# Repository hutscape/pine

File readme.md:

# Pine

> 🌲 Indoor Infrared receiver and transmitter with temperature sensor 🎐

Visit [hutscape.com/pine](https://hutscape.com/pine) for more details.

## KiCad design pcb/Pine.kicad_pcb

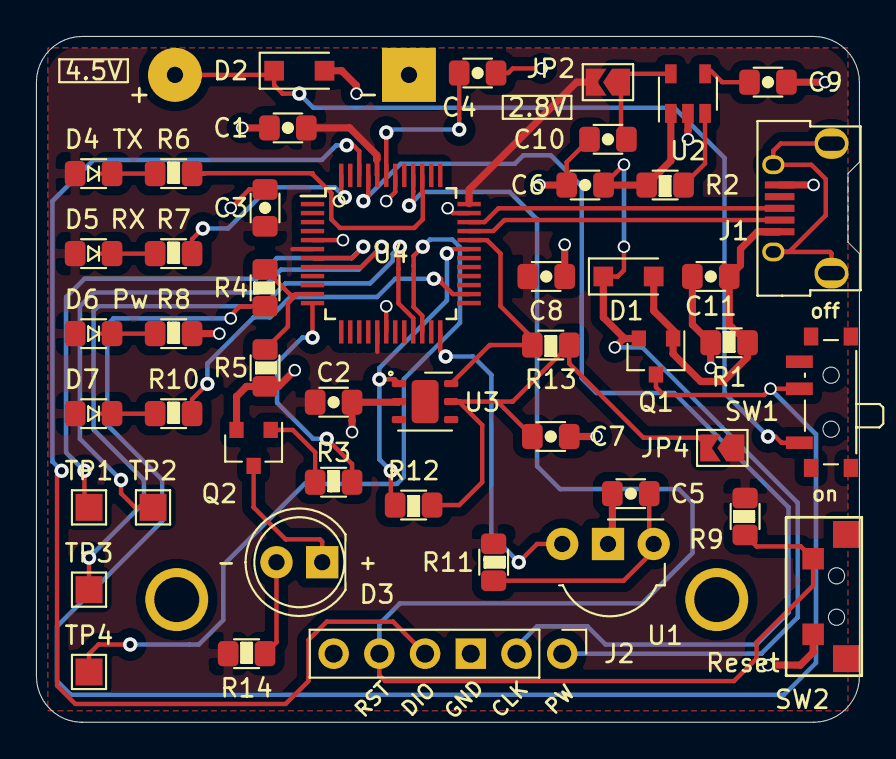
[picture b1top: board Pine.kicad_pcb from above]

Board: 2 copper layers, 45.7 x 38.1 mm, 49 parts (0 on the bottom side), 36 nets.

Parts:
C1, C2, C3: 100nF; C_0805_2012Metric_Pad1.15x1.40mm_HandSolder
C4, C5, C6, C7, C10: 1uF; C_0805_2012Metric_Pad1.15x1.40mm_HandSolder
C8, C11: 10uF; C_0805_2012Metric_Pad1.15x1.40mm_HandSolder
C9: 10nF; C_0805_2012Metric_Pad1.15x1.40mm_HandSolder
D1, D2: Schottky diode; D_SOD-123F
D3: IR LED Emitter; LED_D5.0mm_IRGrey
D4, D5, D6, D7: LED Yellow; LED_0805_2012Metric_Pad1.15x1.40mm_HandSolder
J1: USB Micro type-B; USB_Micro-B_Horizontal-U254-051T-4BH23-S2B
J2: 01x06 Male conn; PinHeader_1x06_P2.54mm_Vertical
J3: Battery connector; BatteryHolder_Takachi_SN3-3PC_3AA
JP2, JP4: Open solder jumper; SolderJumper-2_P1.3mm_Open_TrianglePad1.0x1.5mm
Q1: p-channel MOSFET; SOT-23
Q2: NPN Transistor; SOT-23
R1, R9, R12, R13: 10k; R_0805_2012Metric_Pad1.15x1.40mm_HandSolder
R2, R4, R5: 100k; R_0805_2012Metric_Pad1.15x1.40mm_HandSolder
R3, R6, R7, R8, R10, R11: 470R; R_0805_2012Metric_Pad1.15x1.40mm_HandSolder
R14: 0R; R_0805_2012Metric_Pad1.15x1.40mm_HandSolder
SW1: Switch; SW_SPDT_PCM12
SW2: Push button; Tactile_pushbutton
TP1, TP2, TP3, TP4: TestPoint_Probe; TestPoint_Pad_1.5x1.5mm
U1: IR Receiver; Vishay_MOLD-3Pin
U2: LDO; SOT-23-5
U3: Temperature sensor; DFN-6-1EP_3x3mm_P1mm_EP1.5x2.4mm
U4: MCU; TQFP-48_7x7mm_P0.5mm

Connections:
+2V8: C1.1, C2.1, C3.1, C8.1, D4.2, D5.2, D6.2, D7.2, JP2.2, JP4.1, R9.2, R11.1, R14.1, U4.6, U4.17, U4.36, U4.44
/Batt: R4.2, R5.1, U4.11
/IR_Emitter: R3.2, U4.12
/IR_Receiver: U1.1, U4.24
/LED: R10.2, U4.26
/RST: J2.5, R9.1, SW2.1, U4.40
/RX_LED: R7.2, U4.48
/SCL: R13.2, U3.6, U4.32
/SDA: R12.2, U3.1, U4.31
/SWCLK: J2.2, U4.45
/SWDIO: J2.4, U4.46
/SWD_POWER_IN: C6.1, D1.1, J2.1, Q1.2, R2.2, U2.1
/TX_LED: R6.2, U4.39
/USB_D+: J1.3, U4.34
/USB_D-: J1.2, U4.33
/VBAT: Q1.3, R4.1, SW1.2
GND: C1.2, C2.2, C3.2, C4.1, C5.2, C6.2, C7.2, C8.2, C9.2, C10.2, C11.2, D2.2, J1.5, J2.3, J3.2, Q2.2, R1.1, R5.2, R8.2, SW2.2, U1.2, U2.2, U3.2, U4.5, U4.18, U4.35, U4.42
unnamed: C4.2, U4.43
unnamed: C5.1, R11.2, U1.3
unnamed: C7.1, JP4.2, R12.1, R13.1, U3.5
unnamed: C9.1, U2.4
unnamed: C10.1, JP2.1, U2.5
unnamed: C11.1, D1.2, J1.1, Q1.1, R1.2
unnamed: D2.1, J3.1, SW1.1
unnamed: D3.1, Q2.3
unnamed: D3.2, R14.2
unnamed: D4.1, R6.1
unnamed: D5.1, R7.1
unnamed: D6.1, R8.1
unnamed: D7.1, R10.1
unnamed: Q2.1, R3.1
unnamed: R2.1, U2.3
unnamed: TP1.1, U4.7
unnamed: TP2.1, U4.8
unnamed: TP3.1, U4.21
unnamed: TP4.1, U4.22

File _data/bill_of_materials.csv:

"Designator","Value","Qty","Package","Category","Stock","Manufacturer","MPN","Datasheet","Vendor","Link","Unit","Total","MOQ","Description","DNP"
"C3, C2, C1, ","100nF","3","0805","Electronics","53","Murata Electronics","GCM21BR72A104KA37L","https://www.mouser.sg/datasheet/2/281/murata_03122018_GCM_Se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","LCSC","https://lcsc.com/product-detail/Multilayer-Ceramic-Capacitor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","0.030","0.09","20","C_Small: Unpolarized capacitor, small symbol",""
"C4, C5, C7, C6, C10, ","1uF","5","0805","Electronics","17","","","","Internal stock","","0","0.0","","C_Small: Unpolarized capacitor, small symbol",""
"C8, C11, ","10uF","2","0805","Electronics","30","","","","Internal stock","","0","0.0","","C_Small: Unpolarized capacitor, small symbol",""
"C9, ","10nF","1","0805","Electronics","55","Walsin Tech Corp","0805B103K631CT","https://datasheet.lcsc.com/szlcsc/1811301232_Huaxin-S-T-0805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","LCSC","https://lcsc.com/product-detail/Multilayer-Ceramic-Capacitor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","0.026","0.03","20","C_Small: Unpolarized capacitor, small symbol",""
"D1, D2, ","Schottky diode","2","SOD-123F ","Electronics","52","Nexperia","PMEG3020EH","https://datasheet.lcsc.com/szlcsc/ON-Semicon-ON-MBR230LSFT1G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","RS Components","https://sg.rs-online.com/web/p/rectifier-diodes-schottky-dio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","0.388","0.78","20","D_Schottky: Schottky diode",""
"D3, ","IR LED Emitter","1","TH","Electronics","39","ROHM","SIR-56ST3F ","https://docs-apac.rs-online.com/webdocs/1674/0900766b816747ad.pdf","RS Components","https://sg.rs-online.com/web/p/ir-leds/1780575/?sra=pstk","0.778","0.78","10","LD274: 950nm IR-LED, 5mm",""
"D4, D5, D6, D7, ","LED Yellow","4","0805","Electronics","54","Everlight Elec","17-215UYC/S530-A3/TR8","https://datasheet.lcsc.com/szlcsc/Everlight-Elec-17-215UYC-S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","LCSC","https://lcsc.com/product-detail/Light-Emitting-Diodes-LED_08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","0.058","0.23","10","LED: Light emitting diode","D4, D5, "
"J1, ","USB Micro type-B","1","SMD","Connector","60","Jing Extension of the Electronic Co.","C10418","https://datasheet.lcsc.com/szlcsc/Jing-Extension-of-the-Elec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","LCSC","https://lcsc.com/product-detail/USB-Connectors_Jing-Extensio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","0.079","0.08","5","USB_B_Micro: USB Micro Type B connector",""
"J2, ","01x06 Male conn","1","TH","Connector","","","","","DNP","","","0","","Conn_01x06_Male: Generic connector, single row, 01x06, script generated (kicad-library-utils/schlib/autogen/connector/)","J2, "
"J3, ","Battery connector","1","TH","Connector","","Takachi Electric Industrial","SN3-3PC","https://docs-apac.rs-online.com/webdocs/1659/0900766b81659aed.pdf","RS Components","https://sg.rs-online.com/web/p/products/1756075","2.484","2.48","1","Conn_01x02_Male: Generic connector, single row, 01x02, script generated (kicad-library-utils/schlib/autogen/connector/)",""
"JP2, JP4, ","Open solder jumper","2","Solder","Electronics","","","","","DNP","","","0","","SolderJumper_2_Open: Solder Jumper, 2-pole, open","JP2, JP4, "
"Q1, ","p-channel MOSFET","1","SOT-23","Electronics","49","Nexperia","BSH203,215 ","https://docs-apac.rs-online.com/webdocs/0f74/0900766b80f74f2c.pdf","RS Components","https://sg.rs-online.com/web/p/mosfets/7258366/","0.312","0.31","20","BSS83P: -0.33A Id, -60V Vds, P-Channel MOSFET, SOT-23-3",""
"Q2, ","NPN Transistor","1","SOT-23","Electronics","58","ON Semiconductor","BC817-25LT3G","https://datasheet.lcsc.com/szlcsc/ON-Semicon-ON-BC817-25LT3G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","LCSC","https://lcsc.com/product-detail/Transistors-NPN-PNP_ON-Semic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","0.021","0.02","5","2N2219: 800mA Ic, 50V Vce, NPN Transistor, TO-39",""
"R2, R4, R5, ","100k","3","0805","Electronics","56","RALEC","RTT051003BTP","https://datasheet.lcsc.com/szlcsc/RALEC-RTT051003BTP_C312260.pdf","LCSC","https://lcsc.com/product-detail/Others_RALEC-RTT051003BTP_C3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","0.042","0.13","20","R_Small: Resistor, small symbol",""
"R9, R1, R12, R13, ","10k","4","0805","Electronics","31","","","","Internal stock","","","0","","R_Small: Resistor, small symbol",""
"R10, R11, R3, R8, R7, R6, ","470R","6","0805","Electronics","57","Walsin Tech Corp","WR08X4700FTL","https://datasheet.lcsc.com/szlcsc/Huaxin-S-T-WR08X4700FTL_C1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","LCSC","https://lcsc.com/product-detail/Chip-Resistor-Surface-Mount_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","0.0050 ","0.03","50","R_Small: Resistor, small symbol","R11, R7, R6, "
"R14, ","0R","1","","Electronics","15","","","","Internal stock","","","0","","R_Small: Resistor, small symbol","R14, "
"SW1, ","Switch","1","SMD","Connector","40","","","","Internal stock","","","0","","SW_SPST: Single Pole Single Throw (SPST) switch",""
"SW2, ","Push button","1","SMD","Connector","14","","","","Internal stock","","","0","","SW_Push: Push button switch, generic, two pins",""
"TP1, TP2, TP3, TP4, ","TestPoint_Probe","4","","Electronics","","","","","","","","0","","TestPoint_Probe: test point (alternative probe-style design)","TP1, TP2, TP3, TP4, "
"U1, ","IR Receiver","1","TH","Electronics","38","Vishay","TSOP4838","https://docs-apac.rs-online.com/webdocs/0e30/0900766b80e30b9e.pdf","RS Components","https://sg.rs-online.com/web/p/ir-receivers/7085115/?sra=pstk","1.876","1.88","5","TSOP43xx: IR Receiver Modules for Remote Control Systems",""
"U2, ","LDO","1","SOT-23","Electronics","50","STMicroelectronics","LD3985M28R_SOT23","https://docs-apac.rs-online.com/webdocs/151f/0900766b8151fea1.pdf","RS Components","https://sg.rs-online.com/web/p/low-dropout-voltage-regulator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","0.32","0.32","","LD3985M28R_SOT23: 150mA Low Dropout Voltage Regulator, Fixed Output 2.8V, SOT-23-5",""
"U3, ","Temperature sensor","1","DFN","Electronics","5","Si Labs","Si7021-A20","https://www.silabs.com/documents/public/data-sheets/Si7021-A20.pdf","Internal stock","","","0","","Si7021-A20: I2C Humidity and Temperature Sensor, DFN-6",""
"U4, ","MCU","1","TQFN-48","Electronics","59","Microchip Tech","ATSAMD21G18A-AUT","http://ww1.microchip.com/downloads/en/DeviceDoc/SAMD21-Famil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","LCSC","https://lcsc.com/product-detail/ATMEL-AVR_ATMEL_ATSAMD21G18A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","6.05","6.05","1","ATSAMD21G18A-AUT: SAM D21 Microchip SMART ARM-based Flash MCU, 48Mhz, 256K Flash, 32K SRAM, TQFP-48",""

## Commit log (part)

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2019-07-25 First commit
    Chinmay Pendharkar <notthetup@gmail.com>
2019-07-25 [docs] Remove unused includes from layout
2019-07-25 [docs] Fix readme title
2019-07-25 [docs] update git submodule
2019-08-02 [docs] Tweak user stories
2019-08-02 [docs] Sync design template
2019-08-04 [docs] Change MCU to Atmega328
2019-08-06 [docs] Amend MCU to ATmega32U4
2019-08-06 [firmware] Improve Makefile
2019-08-07 [docs] Add more design references
2019-08-07 [docs] Change MCU to SAMD21
2019-08-15 [docs] Cleanup Makefile
2019-08-15 [docs] Add comparison of SAMD21 and ATmega328p
2019-08-17 [docs] Fix YouTube
2019-08-20 [design] Update firmware for IR receive and emit with SAMD21 board
2019-08-20 [design] Add BOM so far
2019-08-20 [bom] Fix bom generation script if no MPN
2019-08-20 [bom] No fix
2019-08-20 [docs] Remove previous EFM32 prototype image
2019-08-20 [design] Switch to an active /dev/cu.usbmodem port
2019-08-25 [docs] Add some links for power
2019-08-27 [design] Add I2C temperature sensor
2019-08-27 [design] Store IR code in flash
2019-09-02 [design] Add state machine
2019-09-02 [design] Add to user stories
2019-09-02 [design] Add power tree schematic
2019-09-03 [design] Abstract into functions
2019-09-03 [design] Send IR code array to browser
2019-09-04 [design] Display received aircon on and off commands on browser
2019-09-04 [design] Improve user config
2019-09-04 [design] Improve UI in software
2019-09-05 [docs] Add scripts folder as a git submodule
2019-09-08 [docs] Update BOM and script
2019-09-09 [design] Change schematic to draw power from 3.3V only
2019-09-10 [design] Amend power tree schematic
2019-09-11 [design] Update power tree with AP2112 output voltage
2019-09-11 [design] Update schematic with SAMD21 chip instead of dev board
2019-09-11 [docs] Fix link to git submodule
2019-09-11 [design] Update schematic and BOM with Si7021 chip instead of module
2019-09-11 [design] Update schematic with LED circuits
2019-09-11 [design] Update schematic with LED circuit
2019-09-12 [design] Fix MOSFET direction with pins source and drain
2019-09-15 [docs] Add image optimization github workflow
2019-09-15 [design] Add 0ohm resistors for circuit isolation
2019-09-16 [design] Add SWD connector for programming the bootloader
2019-09-16 [design] Update BOM with vendor links
2019-09-16 [docs] Add icons
2019-09-17 [design] Add power management circuit simulation
2019-09-17 [design] Indicate DNP parts
2019-09-18 [docs] Move power images and add circuit simulation video
2019-09-18 [design] Indicate internal stock for BOM
2019-09-19 [design] Add power management circuit simulation without inverter and USB ID pin
2019-09-19 [design] DNP TX/RX LEDs
2019-09-19 [design] Add battery voltage measurement circuit
2019-09-19 [design] Add more info to BOM
2019-09-19 [design] Add passives based on datasheet sample application circuit for IR receiver and sensor
2019-09-22 [design] Add application circuit for new LDO
2019-09-22 [design] Update BOM with more passive for application circuits
2019-09-22 [design] Cleanup BOM
2019-09-22 [design] Design new footprint for USB Micro-B connector
2019-09-23 [design] Associate battery holder with footprint
2019-09-23 [design] Setup initial rat's nest with parts and footprints matched
2019-09-23 [design] Improve power management circuit
2019-10-05 [docs] Remove references from navbar
2019-10-08 ci: add conventional commit style
2019-10-08 ci: add conform to GitHub Actions
2019-10-08 ci: add runs on property to conform for GitHub Actions
2019-10-09 ci: update all submodules initially
2019-10-09 ci: run all ci upon push
2019-10-10 ci: change calibre GitHub action on push to PR only
2019-10-11 feat: add sorting and searching for bom
2019-10-11 fix: change unit cost from string to float for proper sorting
2019-10-12 feat: tweak BOM column header and serial column
2019-10-13 feat: add external link icon beside a vendor link
2019-10-23 feat: place components mechanically with silkscreen annotations
2019-10-24 fix: improve components placement. close #9
2019-10-24 feat: add references for RC circuit and measuring power. close #7
2019-10-24 feat: change footprint to layout naming
2019-10-24 feat: add download buttons on getting started page
2019-10-25 feat: add 4 test points in schematic and layout. close #6
2019-10-26 feat: complete first cut routing with DRC passing
2019-10-27 feat: add new LDO to power component analysis. close #10
2019-10-27 feat: update power tree schematic with new LDO LD3985 output voltage 2.8V
2019-10-27 feat: add links to hardware
2019-10-27 fix: fix links and tag color
2019-10-27 feat: add a note on aircon ir compatibility
2019-10-27 feat: change to a clear LED to depict the 3D of IR emitter:
2019-10-28 feat: add meta data for download buttons on start page
2019-10-28 feat: Add improvements done to current project
2019-10-29 fix: interchange source and drain labels for the MOSFET. #14
2019-10-29 fix: remove redundant solder jumper. #14
2019-10-30 fix: remove BATT_EN and link to GND. #14
2019-10-30 fix: add series resistor to IR LED. #14
2019-10-30 docs: regenerate iBOM
2019-10-30 docs: update BOM with category
2019-10-31 feat: add detailed title block for schematic
2019-10-31 feat: improve annotations in schematic
2019-11-02 feat: send A or B from the browser when recording ON or OFF IR commands
2019-11-03 chore: update all assets before manufacturing
2019-11-03 feat: render gerber files for PCB manufacturing
2019-11-04 docs: add start of manufacturing date
2019-11-04 feat: sort vendor column in BOM and add checkbox
2019-11-07 docs: add lesson learnt on consolidating orders
2019-11-07 feat: add notes for BOM column
2019-11-11 refactor: update schottky diode with another part number
2019-11-16 docs: update stock
2019-11-16 docs: update schedule dates with the end of manufacturing phase
2019-11-17 fix: invert the switch on/off silkscreen. close #17
2019-11-18 chore: update submodules with global and project specific symbols and footprints
2019-11-28 chore: update KiCad 5.1.5
2019-11-29 chore: remove conform github actions to pass the build
2019-12-08 docs: add reference on forum topic for arduino zero bootloader with STLink
2019-12-09 chore: add back ci conform
2020-05-25 chore: update submodules
2020-07-01 feat: add initial test firmware
2020-07-01 refactor: ignore line length in test firmware
2020-07-07 test: add test firmware
2020-07-07 docs: add test serial monitor results
2020-07-13 docs: add reference to IR Kit project
2020-07-29 refactor: update arduino-cli commands
2020-08-11 refactor: remove web files for test
2020-08-11 update: jekyll and kramdown security
2020-08-11 refactor: update dependancies
2020-08-14 feat: add subsystem level design
2020-08-14 feat: add LEDs in subsystem block diagram
2020-09-05 refactor: update arduino-cli version
2020-09-06 fix: add vendor id for arduino zero
2020-09-07 refactor: add debug prints
2020-09-07 refactor: move all sensor code into folder
2020-09-07 refactor: transfer webusb code to seperate folder
2020-09-08 docs: add .vscode to .gitignore
2020-09-08 feat: store captured IR in flash
2020-09-08 docs: add todo tasks
2020-09-16 docs: update hardware schematic and layout files
2020-09-16 docs: update to status completed
2020-09-16 refactor: rename image case
2020-09-17 docs: remove note on ongoing status
2020-10-02 refactor: rename and comment functions
2020-10-03 refactor: add similar project details
2020-10-05 feat: send user config
2020-10-05 fix: fix form validation check by moving the <form> HTML element
2020-10-06 fix: add IR Raw code array length
2020-10-06 docs: remove similar project duplicate notes
2020-10-06 refactor
2020-10-07 docs: add more similar projects
2020-10-12 refactor: replace mpn with name and datasheet_url with url for similar projects
2020-10-18 docs: add LogiTech Harmony 350 as a similar product
2021-03-30 chore(deps): bump kramdown from 2.3.0 to 2.3.1
    Bumps [kramdown](https://github.com/gettalong/kramdown) from 2.3.0 to 2.3.1.
    - [Release notes](https://github.com/gettalong/kramdown/releases)
    - [Changelog](https://github.com/gettalong/kramdown/blob/master/doc/news.page)
    - [Commits](https://github.com/gettalong/kramdown/commits)
2021-03-30 chore: update gems
2021-05-06 chore: update dependancies
2021-06-26 chore: upgrade dependancies
2021-06-27 chore: cleanup dependancies
2021-06-27 chore: remove unused gem
2021-06-28 refactor: remove google analytics
2021-07-13 chore(deps): bump addressable from 2.7.0 to 2.8.0
    Bumps [addressable](https://github.com/sporkmonger/addressable) from 2.7.0 to 2.8.0.
    - [Release notes](https://github.com/sporkmonger/addressable/releases)
    - [Changelog](https://github.com/sporkmonger/addressable/blob/main/CHANGELOG.md)
    - [Commits](https://github.com/sporkmonger/addressable/compare/addressable-2.7.0...addressable-2.8.0)
    ---
    updated-dependencies:
2021-07-15 chore: update addressable dependancy
2021-08-10 fix: remove fixed top navbar
2021-08-23 refactor: combine lessons, references and schedule pages into others
2021-08-26 chore: remove unused page.yml and update submodule
2021-08-26 chore: update layouts and includes
2021-08-26 refator: seperate layouts and includes as submodules
2021-09-10 fix: reset fonts after inserting iBom
2021-10-05 fix: add back content on layout pages
2021-10-08 refactor: reorder tutorials on navbar
2021-10-20 docs: reword prequisites to simpler and similar
2021-11-11 refactor: put the prototype image at the top of examples
2022-01-08 chore: update git submodules
2022-03-09 feat: add favicons to project head
2022-03-09 chore: update anchor.js from 4.2.0 to 4.3.1
2022-03-09 chore: update bulma.css from 0.9.2 to 0.9.3
2022-04-13 docs: remove url in similar project section
2022-04-13 "feat: add monthly progress in scehdule"
2022-04-13 refactor: remove unused version
2022-04-20 "refactor: sync status tags and update footer"
2022-04-20 "refactor: sync status tags for ongoing"
2022-04-20 "refactor: seperate code into more partials"
2022-04-21 refactor: remove repeated status completed tag
2022-04-21 "feat: add new git submodule and install themupon creating new project"
2022-04-21 "refactor: seperate BOM page into more partials"
2022-04-22 "refactor: seperate Example page into more partials"
2022-05-13 feat: update text editor and FreeCAD files in gitignore
2022-05-18 "feat: add 18650 battery 3D model to KiCad library"
2022-05-19 "feat: add /case layout for projects with enclosure designs"
2022-05-19 "refactor: improve FreeCAD file name and link"
2022-07-21 refactor: rename directory from hardware to pcb
2022-07-21 refactor: rename examples to code
2022-07-22 "fix: change GitHub URL for HTML code examples"
2022-07-25 feat: add 3d printed case photos
2022-07-25 refactor: move code list to includes
2023-12-15 chore: update gitsubmodules
2024-02-26 feat: update submodules for unique SMT, DNP and TH BOM parts
2024-02-29 chore: update submodule to fix image url display for relative project paths
2024-02-29 chore: update submodules to seperate /case page into sections
2024-03-04 feat: display all prototype images until defined max_prototype_images
2024-03-15 chore: update submodules to display software bill of materials
2024-03-17 chore: update submodules to display cost and schedule on /others
2024-03-27 refactor: divide others page into csq and resources
2024-03-29 chore: update submodules to remove unused Others page
2024-04-01 chore: update submodule to check Demo code title
2024-04-01 chore: update submodules to hyperlink images
2024-04-11 feat: add a new power page
2024-04-12 chore: update submodules to upgrade to latest JS and CSS libraries
2024-04-12 refactor: simplify putting content on start page with only Markdown
2024-05-04 chore: update submodules to add a link to download demo code
2024-05-04 fix: update broken link for raw content URL
2024-05-06 chore: update submodules to remove unused link to software downloads
2024-05-06 refactor (docs): simplify iteration ideas into one big list
2024-10-11 chore: update submodule to fix checkbox mobile view
2024-11-13 docs: add project name reasoning
2024-11-14 chore: update submodule to conditionally display edit button
